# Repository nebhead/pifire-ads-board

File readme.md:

# PiFire ADS1x15 Module PCB KiCad Files

## What is this? 

This PCB provides an easy way to add an ADS1x15 module to your PiFire build.  This allows you to have up to four different modules in your system, and can be chained together via I2C.  Use the solder jumpers to select a unique I2C address for each of the modules in your system (default is 0x48).  The PCB provides options for JST XH connectors or screw terminals (or if you want to solder wires directly to the board you can always do that too).  Lastly, there are boxes where you can designate the value of the populated resistors, for easy reference once you've built it out.  

The design intent for this board was to make a DIY accessible PCB that can be more easily put together by the maker/enthusiast of almost any skill level.  Full size components are used in most cases and most (if not all) parts should be readily available to order online.  See the [Interactive BOM](#interactive-bom) for more details about the parts used and links to order.

### What is PiFire? 

PiFire is a SBC based Pellet Smoker Controller.  More details can be found [here](https://nebhead.github.io/PiFire) or [at the GitHub repo](https://github.com/nebhead/pifire). 

## What's in this Repository?

### KiCad Project Files 
In this repository you will find the latest KiCad design files for the  PCB.  Simply load the project file (.kicad_pro) into the KiCad software and you should be able to edit as needed.  Or if you just want to get this board made, jump to the production section below.

### Interactive BOM

There is an interactive BOM located in the [/bom](bom/) folder which details the parts and provides some pin information as well.  Use this to gather the components you may need to build this board out and refer back to it for placement help.    

[BOM + Pin Info](https://nebhead.github.io/pifire-ads-board)

_This is a standalone HTML file that was autogenerated by the excellent plugin for KiCad. See the plugin here: [https://github.com/openscopeproject/InteractiveHtmlBom](https://github.com/openscopeproject/InteractiveHtmlBom)_

### PDF of the Schematic

Preview the schematic in PDF format here: [Schematic](pifire-ads-board-schematic.pdf)

### PCB Specific Notes

#### Mounting ADS1115 Device

This intention of this PCB is to have a ADS1115 (or ADS1015) mounted to the top of this board.  You can attach this with a standard pin-header, or directly attaching with solder only.  (see the diagram below showing the ADS1115 attached in the yellow dotted line area)

#### Selecting I2C Address

In addition, you may be able to have up to four of these boards in a single system by assigning different I2C addresses to each device.  These addresses can be selected by using the solder jumpers provided at the bottom of the board.  Simply select the address you want and close/short the solder jumper for that address.  

### JLCPCB Production Files

If you wish to get these PCBs made by JLCPCB, the production files are provided in the `/production` folder.  For convenience, the file `pifire-ads-board-production.zip` can simply be uploaded to JLCPCB to make it super easy to order boards.

Drop the zip file onto the order page, wait for it to upload then simply continue to order the board.  Optionally, select different board color, PCB quantity, surface finish, etc.  Most of the default settings should be sufficient. 

### Links to the PCBs in this family of PiFire Boards

This PCB is part of a family of PCBs that can be used together to create  a full PiFire system.  Generally speaking you need the Main Module/Board, a Relay Control Board and a Probe Device board to have a basic PiFire system.  

**Main Module/Board** (required)
* [Main Board v4.0.x](https://github.com/nebhead/pifire-main-module-nopwr)

**Relay/Fan Control Boards** (choose one)
* [Mechanical Relay Module](https://github.com/nebhead/pifire-relay-module)
* [Solid State Relay Module](https://github.com/nebhead/pifire-relay-module-SSR)
* [Solid State Relay + PWM Fan Module](https://github.com/nebhead/pifire-relay-pwm-module-ssr) - Original Design
* [Solid State Relay + PWM Fan Module Alternate](https://github.com/nebhead/pifire-relay-pwm-module-ssr-alt) - Updated Design (Designed with help from @labmonkeyrat on Discord)

**Probe Device Board** (optional)
* [ADS Board](https://github.com/nebhead/pifire-ads-board) 

### 3D Printable Enclosures/Boxes 

With all of the 3D Prints for PiFire, a higher temperature filament such as PETG should be used.  PLA generally won't stand up to the temperatures that the components may be exposed to outdoors and near a hot smoker.  

#### Enclosure

Included here is an initial revision of the enclosure for this PCB.  The current models should be considered still in development and may have alignment challenges, etc. 

Except for the mounting wings, the majority of bolts to be used with this enclosure are M3. 

* STL: [Base](/printables/PiFire-PCB-v4-ADS-Base.stl)
* STL: [Lid](/printables/PiFire-PCB-v4-ADS-Lid.stl)
* OnShape: [Enclosure Original Models](https://cad.onshape.com/documents/06ff4784dfd59b5ba448a771/w/ff8c53d96188935699d945ec/e/67f72d5e3136186b90fce856?renderMode=0&uiState=66e1183808b48b5751063bbb)

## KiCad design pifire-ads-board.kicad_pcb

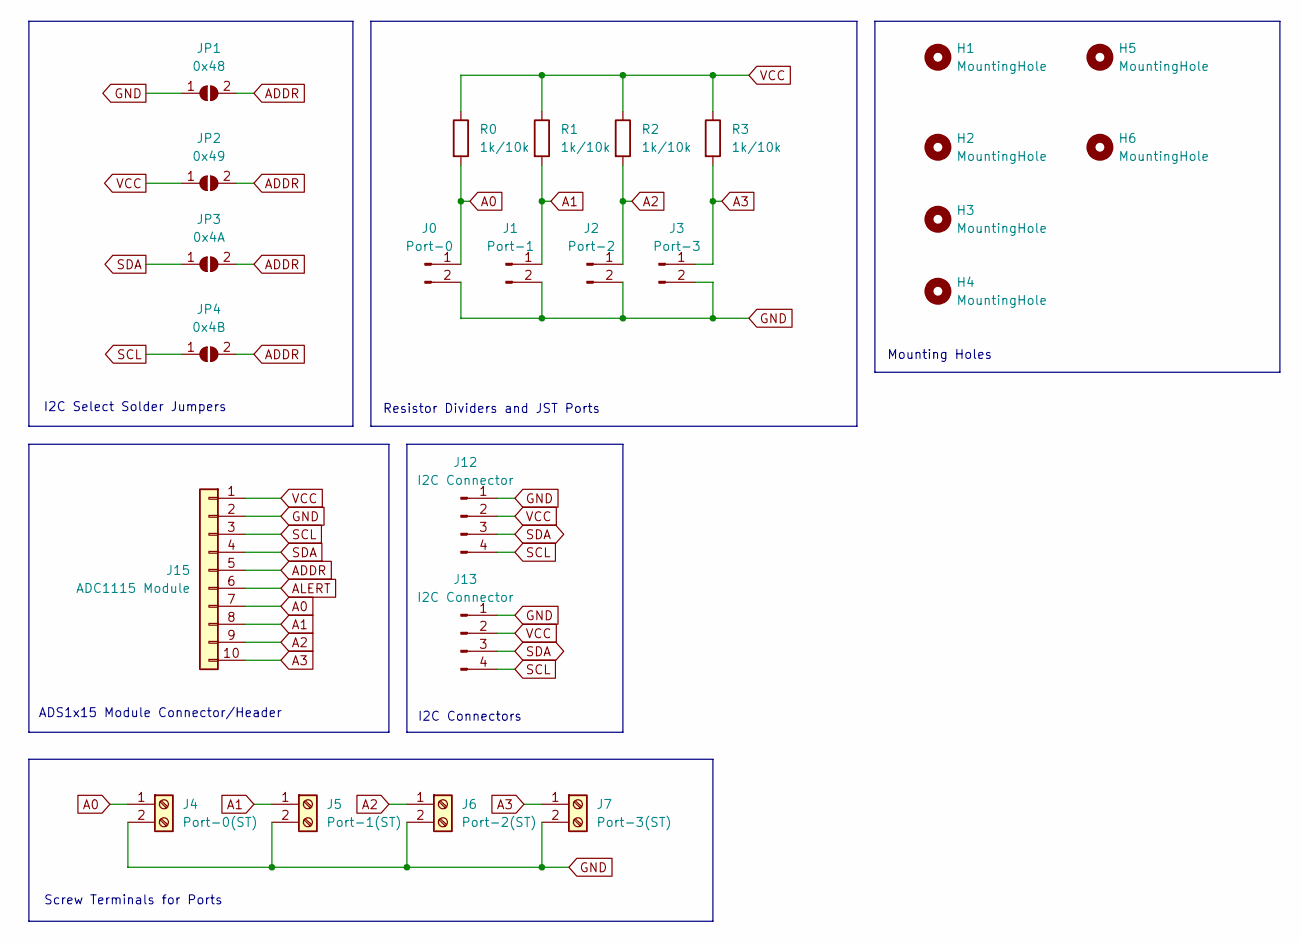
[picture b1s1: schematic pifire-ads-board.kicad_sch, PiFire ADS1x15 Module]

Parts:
H1, H2, H3, H4, H5, H6: MountingHole; MountingHole_3.2mm_M3
J0: Port-0; JST_XH_B2B-XH-A_1x02_P2.50mm_Vertical
J1: Port-1; JST_XH_B2B-XH-A_1x02_P2.50mm_Vertical
J2: Port-2; JST_XH_B2B-XH-A_1x02_P2.50mm_Vertical
J3: Port-3; JST_XH_B2B-XH-A_1x02_P2.50mm_Vertical
J4: Port-0(ST); TerminalBlock_bornier-2_P5.08mm
J5: Port-1(ST); TerminalBlock_bornier-2_P5.08mm
J6: Port-2(ST); TerminalBlock_bornier-2_P5.08mm
J7: Port-3(ST); TerminalBlock_bornier-2_P5.08mm
J12, J13: I2C Connector; JST_XH_S4B-XH-A_1x04_P2.50mm_Horizontal
J15: ADC1115 Module; PinHeader_1x10_P2.54mm_Vertical
JP1: 0x48; SolderJumper-2_P1.3mm_Open_TrianglePad1.0x1.5mm
JP2: 0x49; SolderJumper-2_P1.3mm_Open_TrianglePad1.0x1.5mm
JP3: 0x4A; SolderJumper-2_P1.3mm_Open_TrianglePad1.0x1.5mm
JP4: 0x4B; SolderJumper-2_P1.3mm_Open_TrianglePad1.0x1.5mm
R0, R1, R2, R3: 1k/10k; R_Axial_DIN0207_L6.3mm_D2.5mm_P7.62mm_Horizontal

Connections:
A0: J0.1, J4.1, J15.7, R0.2
A1: J1.1, J5.1, J15.8, R1.2
A2: J2.1, J6.1, J15.9, R2.2
A3: J3.1, J7.1, J15.10, R3.2
ADDR: J15.5, JP1.2 (B), JP2.2 (B), JP3.2 (B), JP4.2 (B)
ALERT: J15.6
GND: J0.2, J1.2, J2.2, J3.2, J4.2, J5.2, J6.2, J7.2, J12.1, J13.1, J15.2, JP1.1 (A)
SCL: J12.4, J13.4, J15.3, JP4.1 (A)
SDA: J12.3, J13.3, J15.4, JP3.1 (A)
VCC: J12.2, J13.2, J15.1, JP2.1 (A), R0.1, R1.1, R2.1, R3.1

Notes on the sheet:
Screw Terminals for Ports
ADS1x15 Module Connector/Header
I2C Select Solder Jumpers
Resistor Dividers and JST Ports
Mounting Holes
I2C Connectors

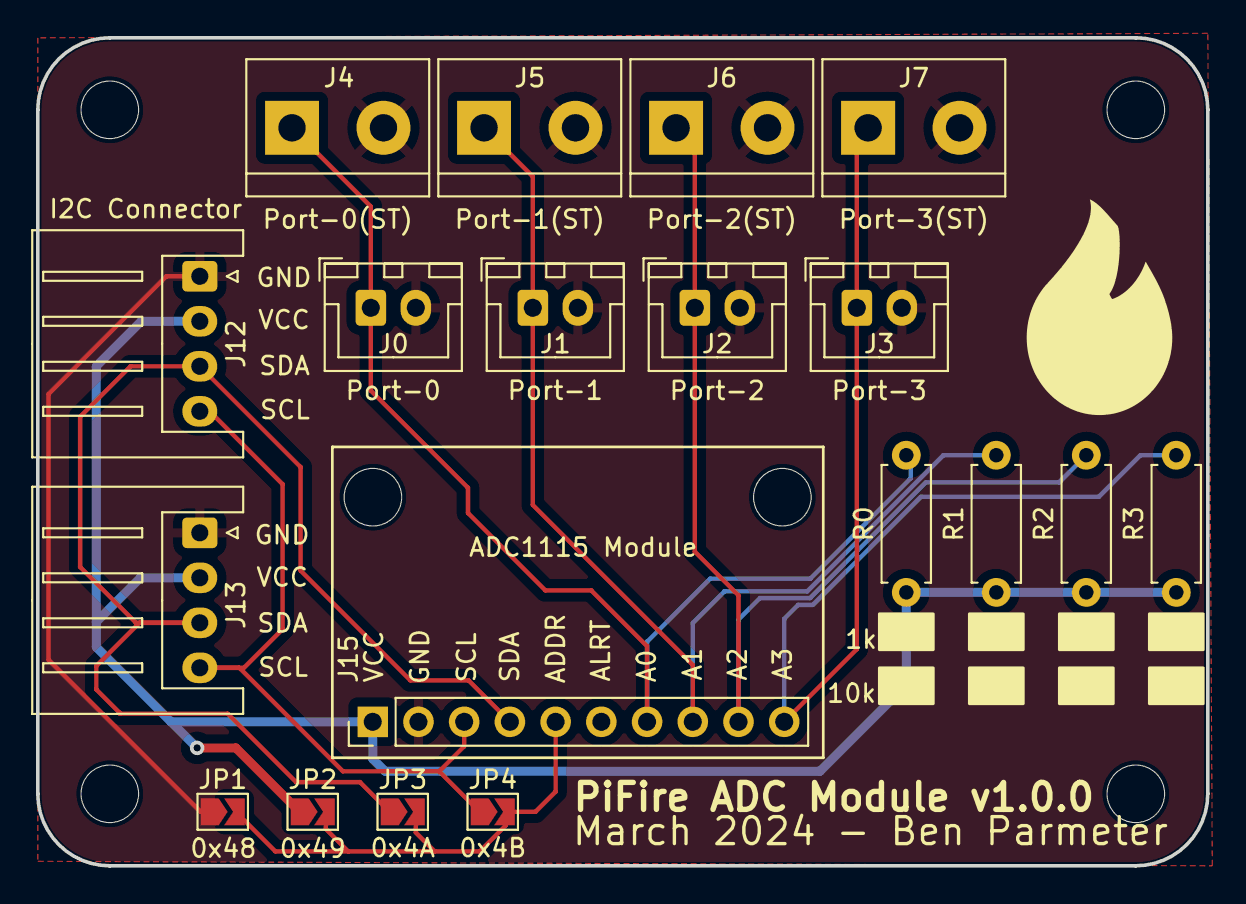
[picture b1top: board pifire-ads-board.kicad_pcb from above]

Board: 2 copper layers, 65.0 x 46.0 mm, 25 parts (0 on the bottom side), 9 nets.

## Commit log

2024-05-03 Adding .gitignore
    Adding ignored files & folders to gitignore.
2024-05-03 Move BOM to index.html
    Add link to interactive BOM to readme.md
2024-05-03 Fix link to documentation
2024-05-10 Updated Documentation
2024-09-07 Update readme.md
    Add PWM Board links.
2024-09-11 Added 3D Printables
2025-12-01 Fix ADS Lid 3D Print STL
    Fix the ADS Board 3D Print Lid STL file.
